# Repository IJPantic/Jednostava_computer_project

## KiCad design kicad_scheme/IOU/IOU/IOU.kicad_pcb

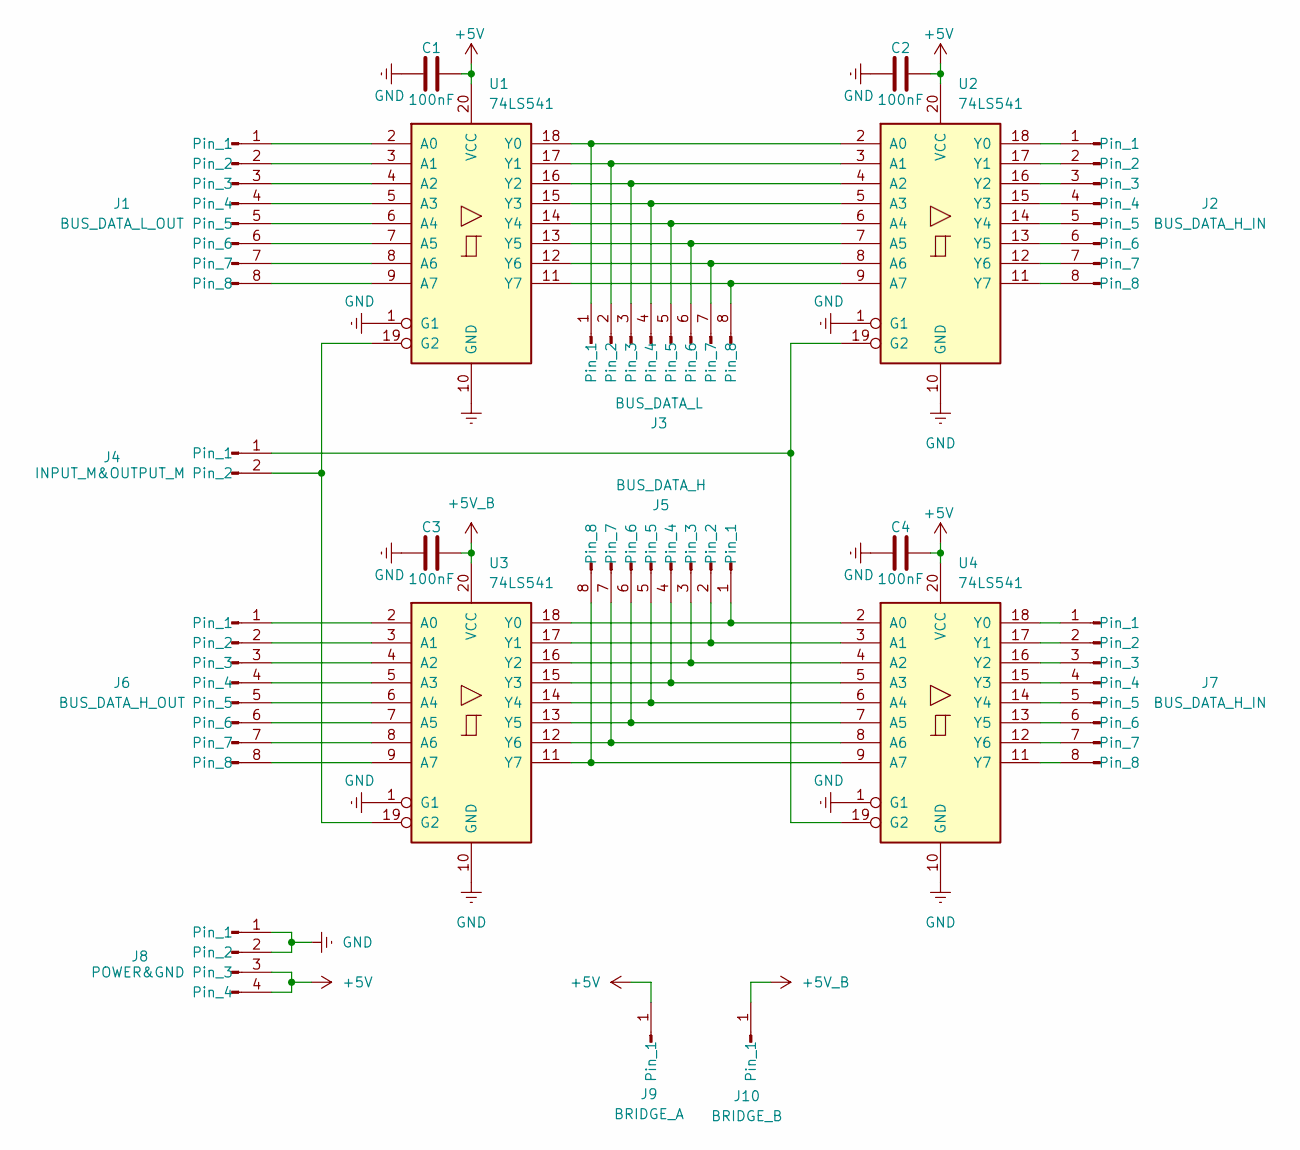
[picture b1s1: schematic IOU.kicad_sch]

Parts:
C1, C2, C3, C4: 100nF; C_Disc_D10.0mm_W2.5mm_P5.00mm
J1: BUS_DATA_L_OUT; PinHeader_1x08_P2.54mm_Vertical
J2, J7: BUS_DATA_H_IN; PinHeader_1x08_P2.54mm_Vertical
J3: BUS_DATA_L; PinHeader_1x08_P2.54mm_Vertical
J4: INPUT_M&OUTPUT_M; PinHeader_1x02_P2.54mm_Vertical
J5: BUS_DATA_H; PinHeader_1x08_P2.54mm_Vertical
J6: BUS_DATA_H_OUT; PinHeader_1x08_P2.54mm_Vertical
J8: POWER&GND; PinHeader_1x04_P2.54mm_Vertical
J9: BRIDGE_A; SolderWire-0.25sqmm_1x01_D0.65mm_OD1.7mm
J10: BRIDGE_B; SolderWire-0.25sqmm_1x01_D0.65mm_OD1.7mm
U1, U2, U3, U4: 74LS541; DIP-20_W7.62mm_Socket

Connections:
+5V: C1.2, C2.2, C4.2, J8.3, J8.4, J9.1 (Pin_1_1), U1.20 (VCC), U2.20 (VCC), U4.20 (VCC)
+5V_B: C3.2, J10.1 (Pin_1_1), U3.20 (VCC)
GND: C1.1, C2.1, C3.1, C4.1, J8.1, J8.2, U1.1 (G1), U1.10 (GND), U2.1 (G1), U2.10 (GND), U3.1 (G1), U3.10 (GND), U4.1 (G1), U4.10 (GND)
unnamed: J1.1, U1.2 (A0)
unnamed: J1.2, U1.3 (A1)
unnamed: J1.3, U1.4 (A2)
unnamed: J1.4, U1.5 (A3)
unnamed: J1.5, U1.6 (A4)
unnamed: J1.6, U1.7 (A5)
unnamed: J1.7, U1.8 (A6)
unnamed: J1.8, U1.9 (A7)
unnamed: J2.1, U2.18 (Y0)
unnamed: J2.2, U2.17 (Y1)
unnamed: J2.3, U2.16 (Y2)
unnamed: J2.4, U2.15 (Y3)
unnamed: J2.5, U2.14 (Y4)
unnamed: J2.6, U2.13 (Y5)
unnamed: J2.7, U2.12 (Y6)
unnamed: J2.8, U2.11 (Y7)
unnamed: J3.1, U1.18 (Y0), U2.2 (A0)
unnamed: J3.2, U1.17 (Y1), U2.3 (A1)
unnamed: J3.3, U1.16 (Y2), U2.4 (A2)
unnamed: J3.4, U1.15 (Y3), U2.5 (A3)
unnamed: J3.5, U1.14 (Y4), U2.6 (A4)
unnamed: J3.6, U1.13 (Y5), U2.7 (A5)
unnamed: J3.7, U1.12 (Y6), U2.8 (A6)
unnamed: J3.8, U1.11 (Y7), U2.9 (A7)
unnamed: J4.1, U2.19 (G2), U4.19 (G2)
unnamed: J4.2, U1.19 (G2), U3.19 (G2)
unnamed: J5.1, U3.18 (Y0), U4.2 (A0)
unnamed: J5.2, U3.17 (Y1), U4.3 (A1)
unnamed: J5.3, U3.16 (Y2), U4.4 (A2)
unnamed: J5.4, U3.15 (Y3), U4.5 (A3)
unnamed: J5.5, U3.14 (Y4), U4.6 (A4)
unnamed: J5.6, U3.13 (Y5), U4.7 (A5)
unnamed: J5.7, U3.12 (Y6), U4.8 (A6)
unnamed: J5.8, U3.11 (Y7), U4.9 (A7)
unnamed: J6.1, U3.2 (A0)
unnamed: J6.2, U3.3 (A1)
unnamed: J6.3, U3.4 (A2)
unnamed: J6.4, U3.5 (A3)
unnamed: J6.5, U3.6 (A4)
unnamed: J6.6, U3.7 (A5)
unnamed: J6.7, U3.8 (A6)
unnamed: J6.8, U3.9 (A7)
unnamed: J7.1, U4.18 (Y0)
unnamed: J7.2, U4.17 (Y1)
unnamed: J7.3, U4.16 (Y2)
unnamed: J7.4, U4.15 (Y3)
unnamed: J7.5, U4.14 (Y4)
unnamed: J7.6, U4.13 (Y5)
unnamed: J7.7, U4.12 (Y6)
unnamed: J7.8, U4.11 (Y7)

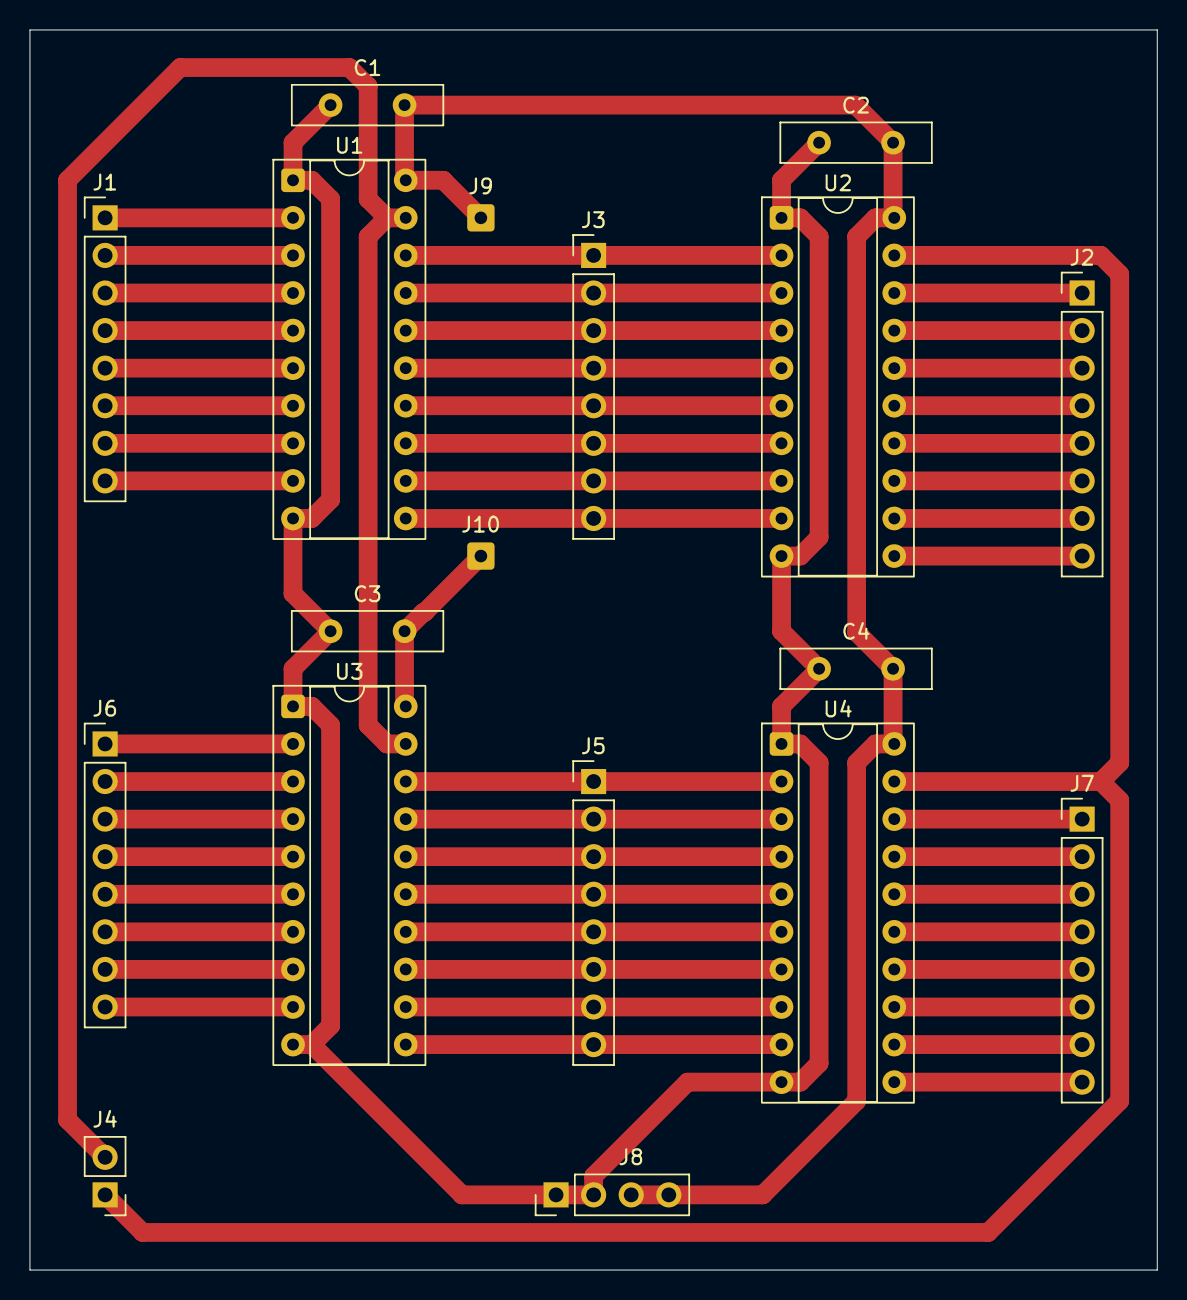
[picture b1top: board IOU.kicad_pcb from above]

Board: 2 copper layers, 76.2 x 83.8 mm, 18 parts (0 on the bottom side), 53 nets.

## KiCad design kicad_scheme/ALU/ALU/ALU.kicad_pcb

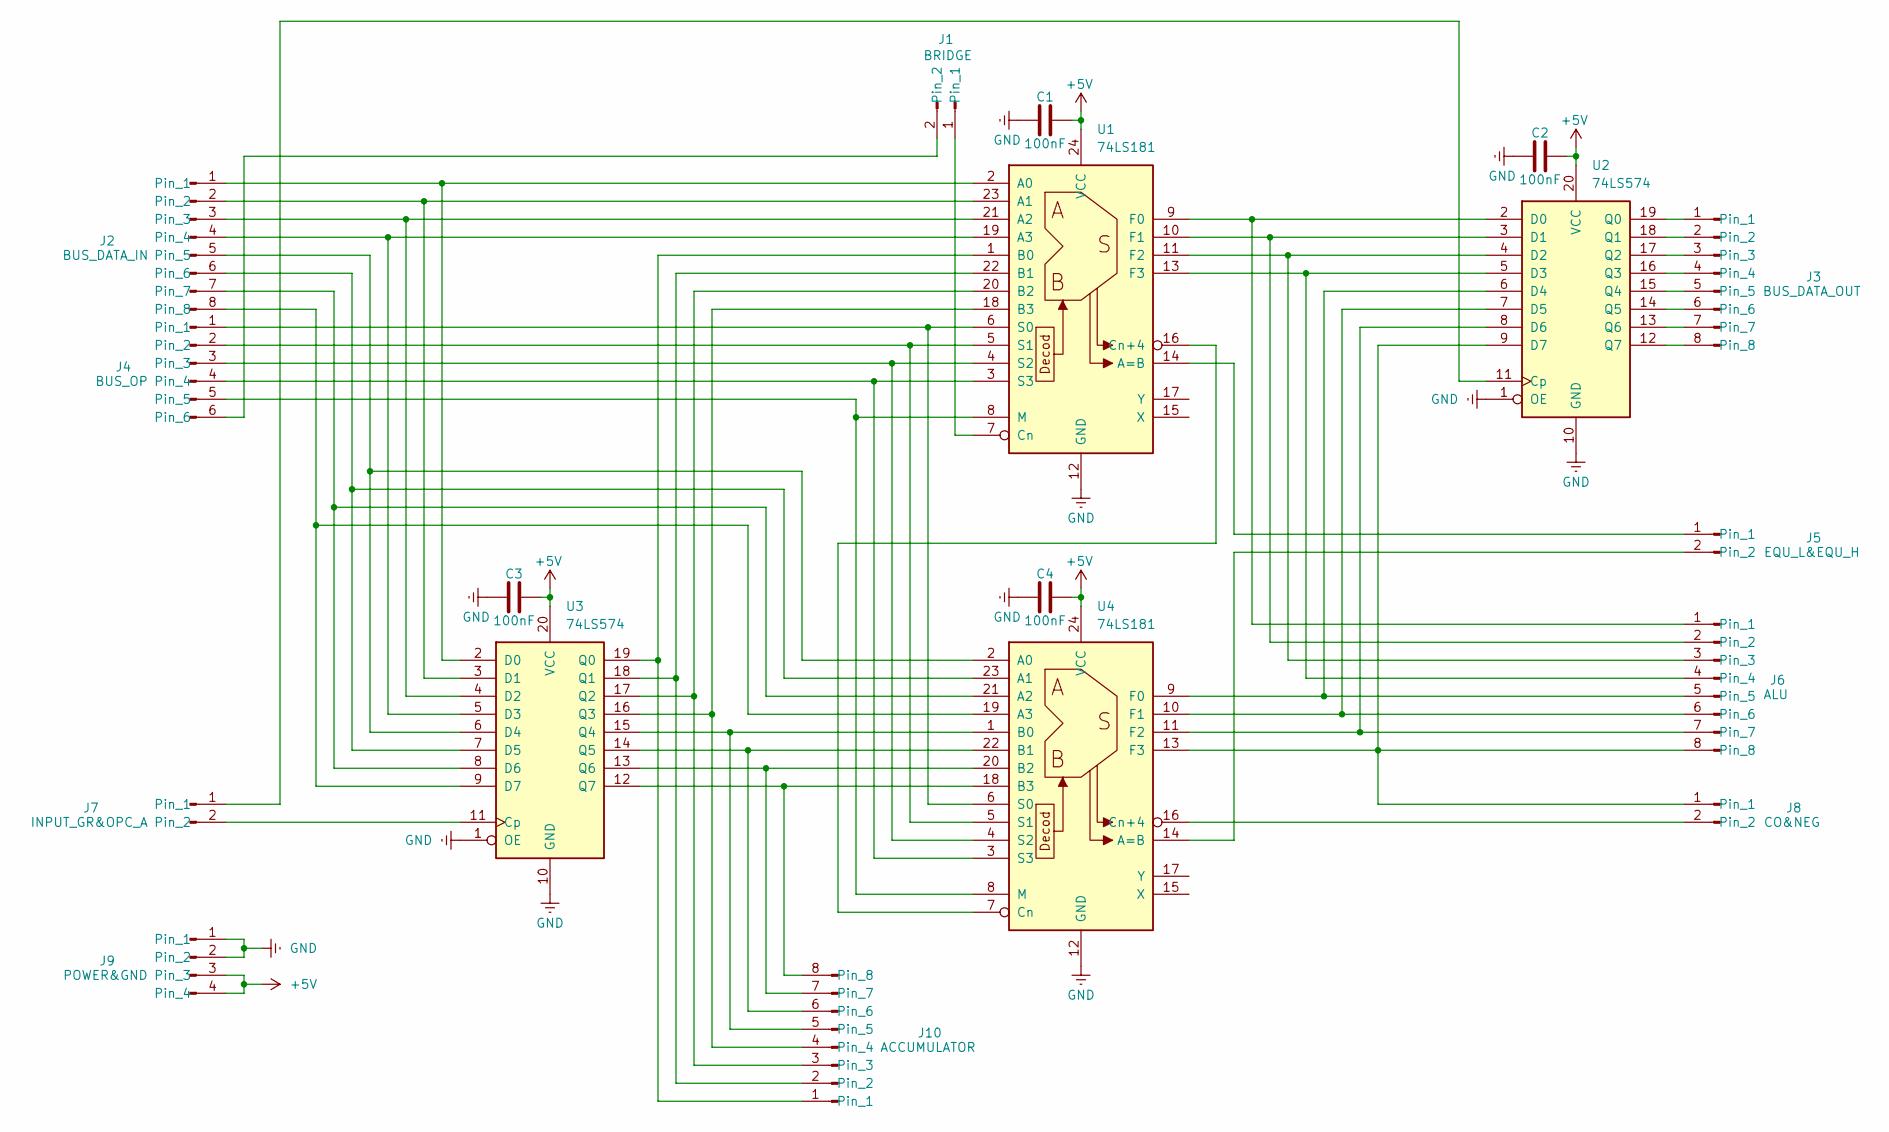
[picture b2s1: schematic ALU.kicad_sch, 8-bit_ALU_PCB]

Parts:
C1, C2, C3, C4: 100nF; C_Disc_D10.0mm_W2.5mm_P5.00mm
J1: BRIDGE; PinHeader_1x02_P2.54mm_Vertical
J2: BUS_DATA_IN; PinHeader_1x08_P2.54mm_Vertical
J3: BUS_DATA_OUT; PinHeader_1x08_P2.54mm_Vertical
J4: BUS_OP; PinHeader_1x06_P2.54mm_Vertical
J5: EQU_L&EQU_H; PinHeader_1x02_P2.54mm_Vertical
J6: ALU; PinHeader_1x08_P2.54mm_Vertical
J7: INPUT_GR&OPC_A; PinHeader_1x02_P2.54mm_Vertical
J8: CO&NEG; PinHeader_1x02_P2.54mm_Vertical
J9: POWER&GND; PinHeader_1x04_P2.54mm_Vertical
J10: ACCUMULATOR; PinHeader_1x08_P2.54mm_Vertical
U1, U4: 74LS181; DIP-24_W15.24mm_Socket
U2, U3: 74LS574; DIP-20_W7.62mm_Socket

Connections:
+5V: C1.2, C2.2, C3.2, C4.2, J9.3, J9.4, U1.24 (VCC), U2.20 (VCC), U3.20 (VCC), U4.24 (VCC)
GND: C1.1, C2.1, C3.1, C4.1, J9.1, J9.2, U1.12 (GND), U2.1 (OE), U2.10 (GND), U3.1 (OE), U3.10 (GND), U4.12 (GND)
unnamed: J1.1, U1.7 (Cn)
unnamed: J1.2, J4.6
unnamed: J2.1, U1.2 (A0), U3.2 (D0)
unnamed: J2.2, U1.23 (A1), U3.3 (D1)
unnamed: J2.3, U1.21 (A2), U3.4 (D2)
unnamed: J2.4, U1.19 (A3), U3.5 (D3)
unnamed: J2.5, U3.6 (D4), U4.2 (A0)
unnamed: J2.6, U3.7 (D5), U4.23 (A1)
unnamed: J2.7, U3.8 (D6), U4.21 (A2)
unnamed: J2.8, U3.9 (D7), U4.19 (A3)
unnamed: J3.1, U2.19 (Q0)
unnamed: J3.2, U2.18 (Q1)
unnamed: J3.3, U2.17 (Q2)
unnamed: J3.4, U2.16 (Q3)
unnamed: J3.5, U2.15 (Q4)
unnamed: J3.6, U2.14 (Q5)
unnamed: J3.7, U2.13 (Q6)
unnamed: J3.8, U2.12 (Q7)
unnamed: J4.1, U1.6 (S0), U4.6 (S0)
unnamed: J4.2, U1.5 (S1), U4.5 (S1)
unnamed: J4.3, U1.4 (S2), U4.4 (S2)
unnamed: J4.4, U1.3 (S3), U4.3 (S3)
unnamed: J4.5, U1.8 (M), U4.8 (M)
unnamed: J5.1, U1.14 (A=B)
unnamed: J5.2, U4.14 (A=B)
unnamed: J6.1, U1.9 (F0), U2.2 (D0)
unnamed: J6.2, U1.10 (F1), U2.3 (D1)
unnamed: J6.3, U1.11 (F2), U2.4 (D2)
unnamed: J6.4, U1.13 (F3), U2.5 (D3)
unnamed: J6.5, U2.6 (D4), U4.9 (F0)
unnamed: J6.6, U2.7 (D5), U4.10 (F1)
unnamed: J6.7, U2.8 (D6), U4.11 (F2)
unnamed: J6.8, J8.1, U2.9 (D7), U4.13 (F3)
unnamed: J7.1, U2.11 (Cp)
unnamed: J7.2, U3.11 (Cp)
unnamed: J8.2, U4.16 (Cn+4)
unnamed: J10.1, U1.1 (B0), U3.19 (Q0)
unnamed: J10.2, U1.22 (B1), U3.18 (Q1)
unnamed: J10.3, U1.20 (B2), U3.17 (Q2)
unnamed: J10.4, U1.18 (B3), U3.16 (Q3)
unnamed: J10.5, U3.15 (Q4), U4.1 (B0)
unnamed: J10.6, U3.14 (Q5), U4.22 (B1)
unnamed: J10.7, U3.13 (Q6), U4.20 (B2)
unnamed: J10.8, U3.12 (Q7), U4.18 (B3)
unnamed: U1.16 (Cn+4), U4.7 (Cn)

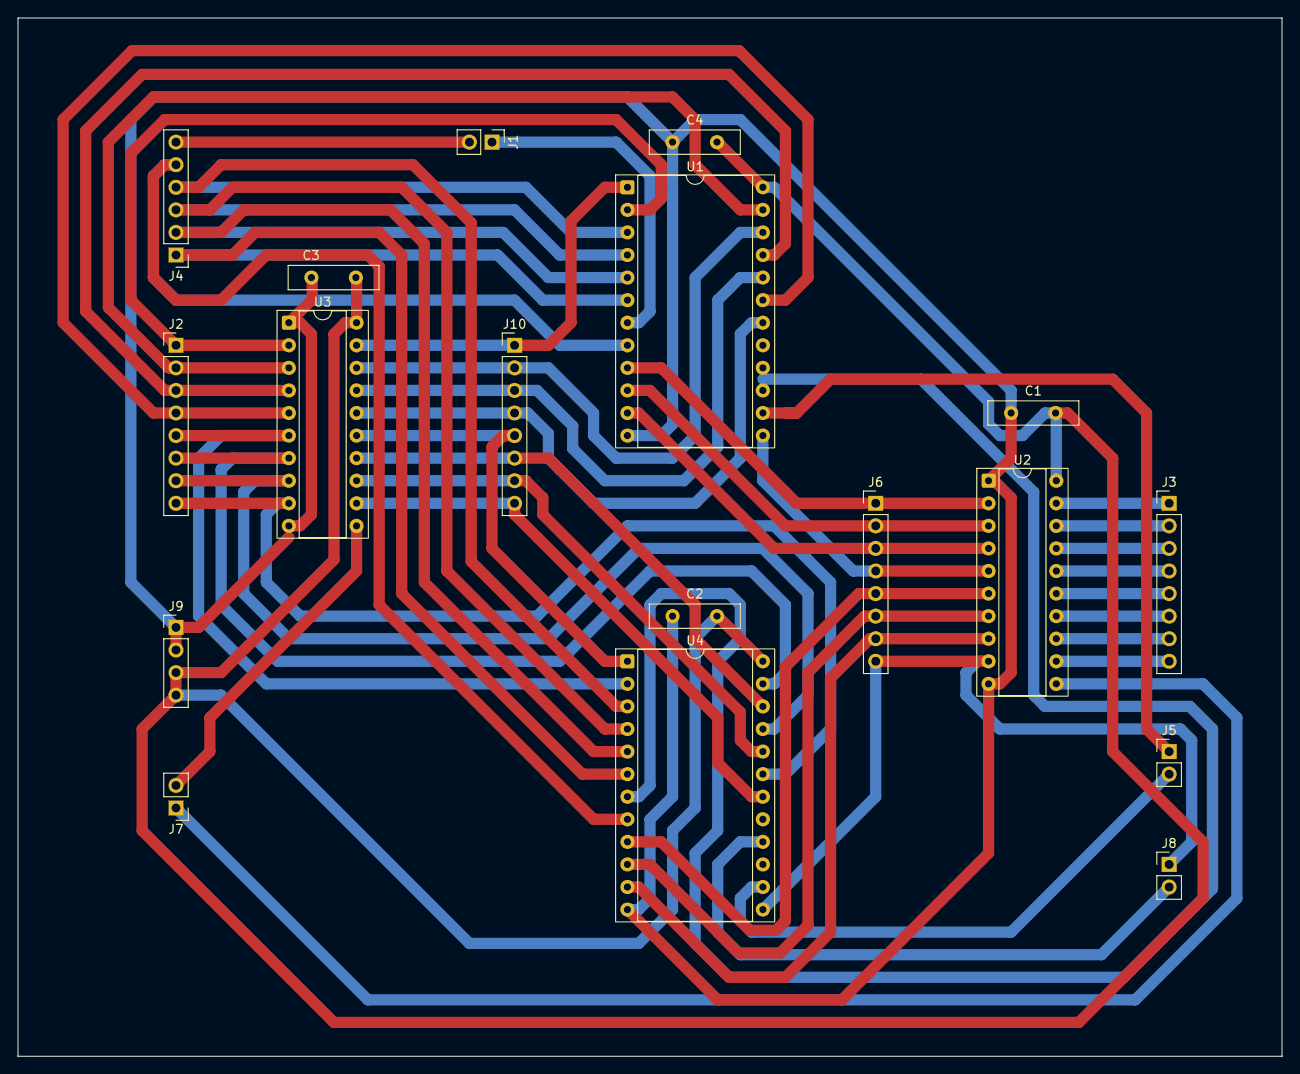
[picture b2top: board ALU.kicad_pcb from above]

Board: 2 copper layers, 142.2 x 116.8 mm, 18 parts (0 on the bottom side), 47 nets.

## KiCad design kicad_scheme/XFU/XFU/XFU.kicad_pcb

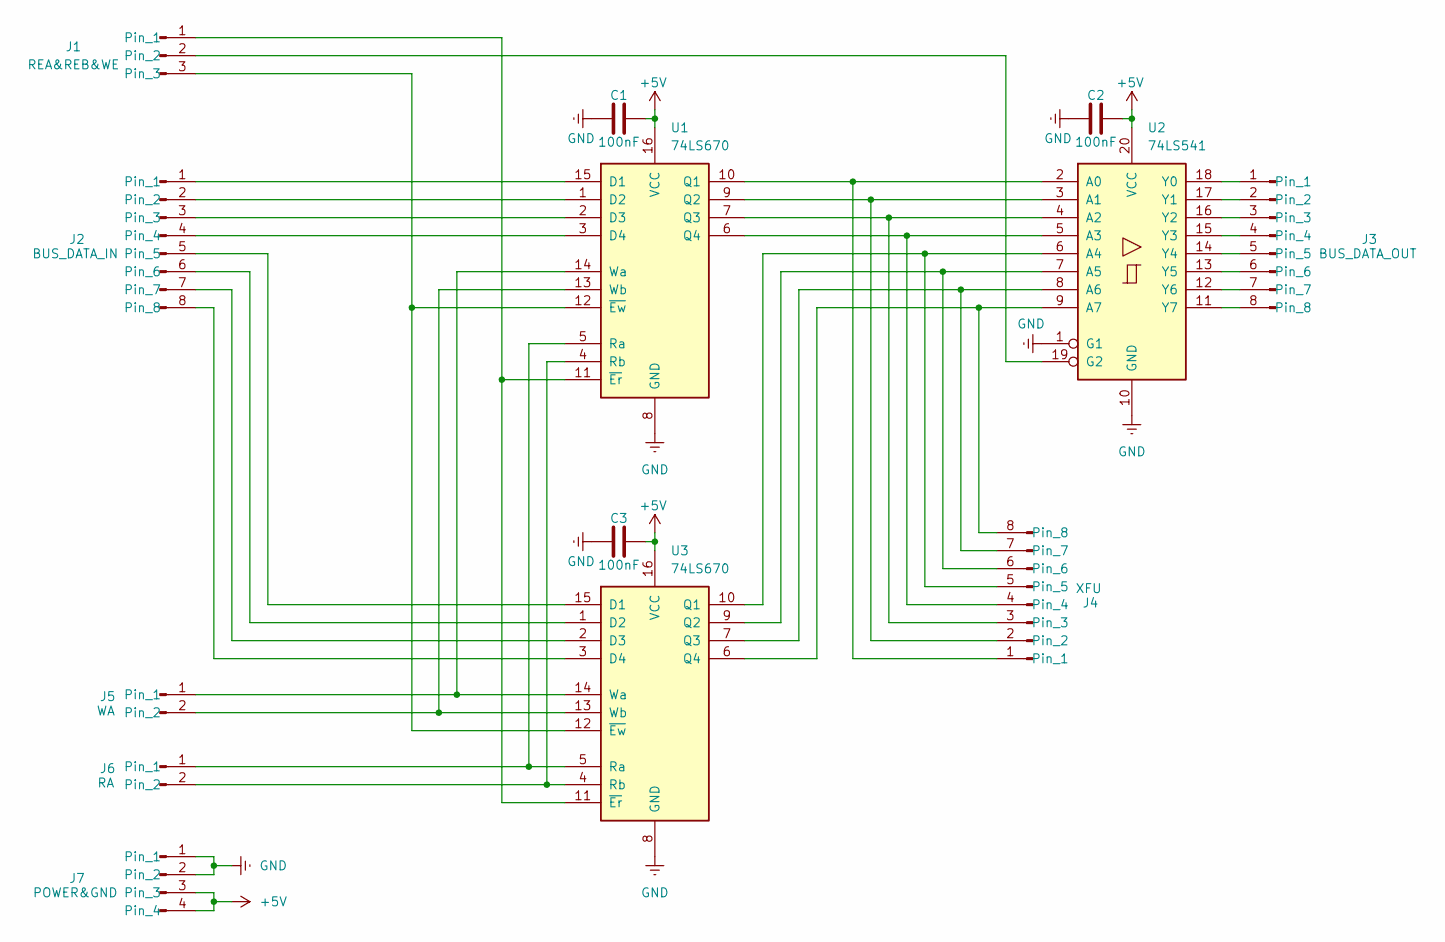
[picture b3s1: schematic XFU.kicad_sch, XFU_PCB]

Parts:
C1, C2, C3: 100nF; C_Disc_D10.0mm_W2.5mm_P5.00mm
J1: REA&REB&WE; PinHeader_1x03_P2.54mm_Vertical
J2: BUS_DATA_IN; PinHeader_1x08_P2.54mm_Vertical
J3: BUS_DATA_OUT; PinHeader_1x08_P2.54mm_Vertical
J4: XFU; PinHeader_1x08_P2.54mm_Vertical
J5: WA; PinHeader_1x02_P2.54mm_Vertical
J6: RA; PinHeader_1x02_P2.54mm_Vertical
J7: POWER&GND; PinHeader_1x04_P2.54mm_Vertical
U1, U3: 74LS670; DIP-16_W7.62mm_Socket
U2: 74LS541; DIP-20_W7.62mm

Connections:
+5V: C1.2, C2.2, C3.2, J7.3, J7.4, U1.16 (VCC), U2.20 (VCC), U3.16 (VCC)
GND: C1.1, C2.1, C3.1, J7.1, J7.2, U1.8 (GND), U2.1 (G1), U2.10 (GND), U3.8 (GND)
unnamed: J1.1, U1.11 (~Er), U3.11 (~Er)
unnamed: J1.2, U2.19 (G2)
unnamed: J1.3, U1.12 (~Ew), U3.12 (~Ew)
unnamed: J2.1, U1.15 (D1)
unnamed: J2.2, U1.1 (D2)
unnamed: J2.3, U1.2 (D3)
unnamed: J2.4, U1.3 (D4)
unnamed: J2.5, U3.15 (D1)
unnamed: J2.6, U3.1 (D2)
unnamed: J2.7, U3.2 (D3)
unnamed: J2.8, U3.3 (D4)
unnamed: J3.1, U2.18 (Y0)
unnamed: J3.2, U2.17 (Y1)
unnamed: J3.3, U2.16 (Y2)
unnamed: J3.4, U2.15 (Y3)
unnamed: J3.5, U2.14 (Y4)
unnamed: J3.6, U2.13 (Y5)
unnamed: J3.7, U2.12 (Y6)
unnamed: J3.8, U2.11 (Y7)
unnamed: J4.1, U1.10 (Q1), U2.2 (A0)
unnamed: J4.2, U1.9 (Q2), U2.3 (A1)
unnamed: J4.3, U1.7 (Q3), U2.4 (A2)
unnamed: J4.4, U1.6 (Q4), U2.5 (A3)
unnamed: J4.5, U2.6 (A4), U3.10 (Q1)
unnamed: J4.6, U2.7 (A5), U3.9 (Q2)
unnamed: J4.7, U2.8 (A6), U3.7 (Q3)
unnamed: J4.8, U2.9 (A7), U3.6 (Q4)
unnamed: J5.1, U1.14 (Wa), U3.14 (Wa)
unnamed: J5.2, U1.13 (Wb), U3.13 (Wb)
unnamed: J6.1, U1.5 (Ra), U3.5 (Ra)
unnamed: J6.2, U1.4 (Rb), U3.4 (Rb)

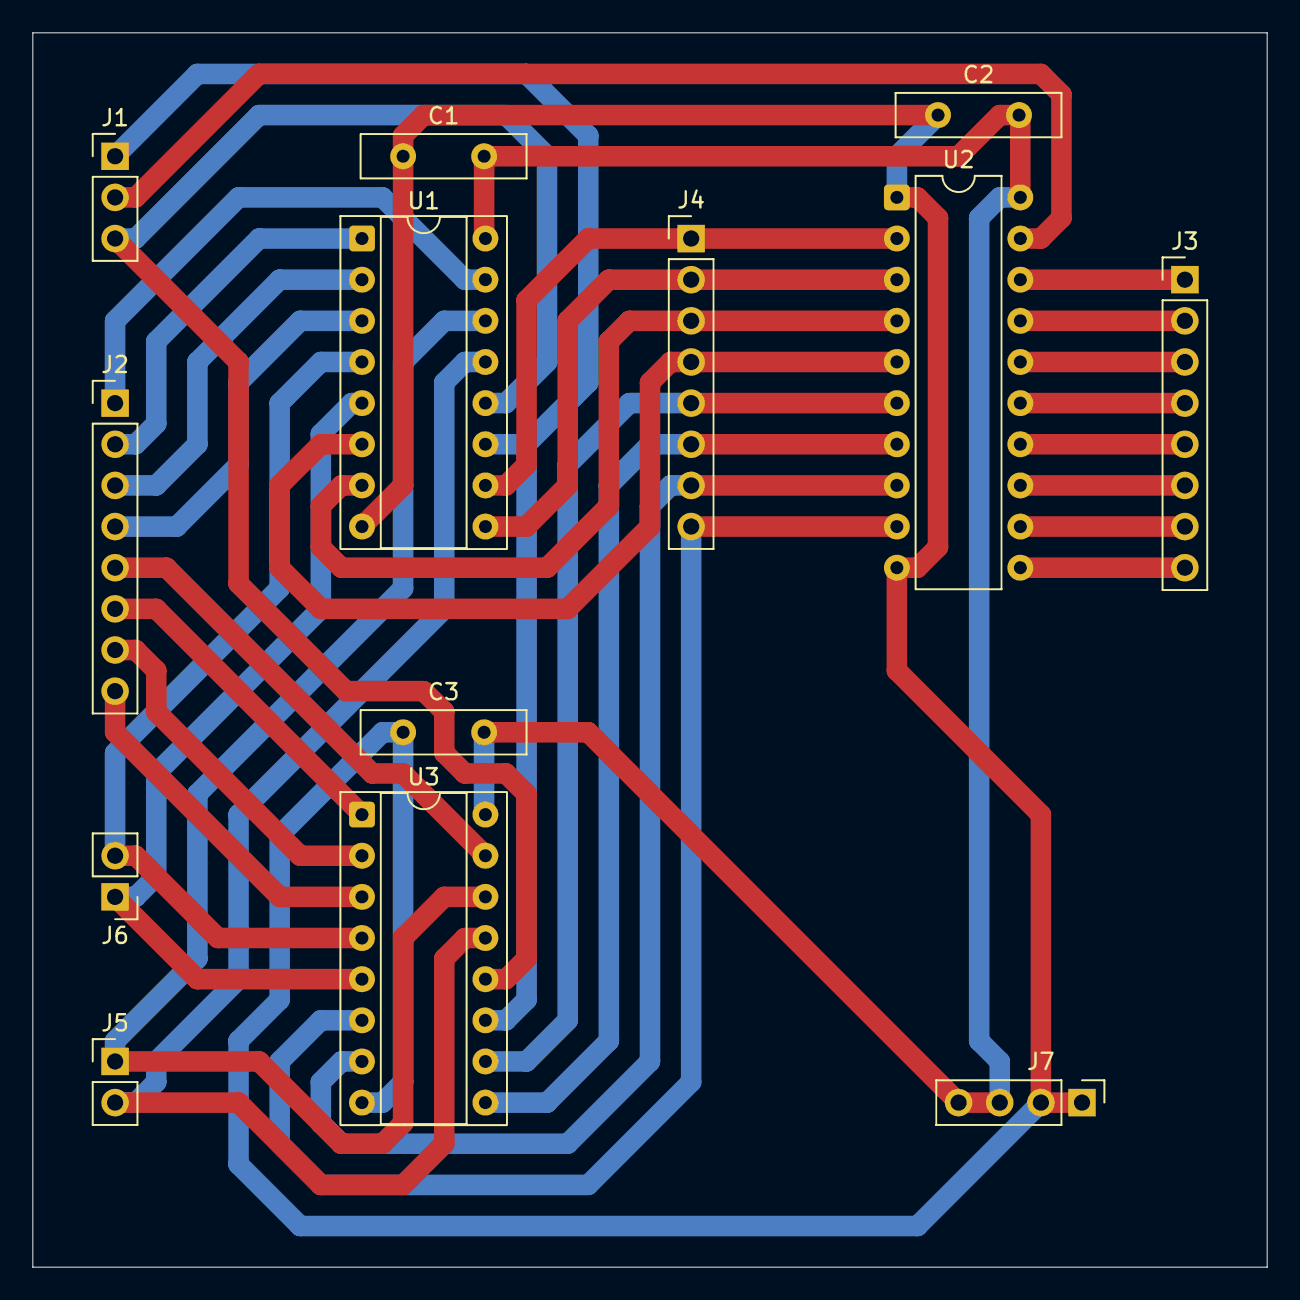
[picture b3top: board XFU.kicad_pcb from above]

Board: 2 copper layers, 76.2 x 76.2 mm, 13 parts (0 on the bottom side), 33 nets.
